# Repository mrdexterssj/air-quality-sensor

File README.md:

# Air quality sensor with OLED screen

A custom CO2 detector that displays the information on an OLED screen and has a LED Alarm. Made for Half Life W4! #YSWS

## Features 

* Uses the MQ-135 air quality sensor to detect the ppm os different nocive gases present in the air surrounding the device
* Has an 0.96 inches OLED screen to display the sensor's information and recommendations
* Has an alarm feature, where if the ppm exceed a certain threshold, an LED starts blinking and the screen shows a warning
* The alarm includes a buzzer that makes sounds at the same time the LED blinks (not added to the firmware yet)
* It also has a button the user can click to snooze the alarm for a minute. After that time passes, the sensor may trigger the alarm again if the ppm hadn't dropped below the predefined threshold
* It uses a XIAO-ESP32-C3 as the microcontroller

## Firmware

The firmware is a python script designed to run in MicroPython. It uses the standard libraries, together with an [external libaray](https://github.com/rubfi/MQ135) to get the readings from the MQ-135 module, and MicroPython's official [ssd1306](https://github.com/micropython/micropython-lib/blob/master/micropython/drivers/display/ssd1306/ssd1306.py) library. 

All the firmware can be found in `/firmware`.

The firmware was written in VSCode, using the `micropython-stubs` pip package, installed in a venv, with some special settings found in `/.vscode/settings.json`

## Production

Gerbers were generated using `Fabrication Toolkit`, a KiCad plugin that generates gerbers and drill files following JLCPCB guidelines and requirements.

They can be found inside `/co2-detector/production` as files, and compressed in `/gerbers.zip`.

## BOM Table

| **Item**                 | **Qty** | **Supplier**  | **Cost/item** | **Total Cost** | **link**                                                                                                                                            | **Note**                                                                    |
|--------------------------|---------|---------------|---------------|----------------|-----------------------------------------------------------------------------------------------------------------------------------------------------|-----------------------------------------------------------------------------|
| 0.96 OLED                | 1       | Temu          | $5.00         | $5.00          | https://www.temu.com/ec/2-piezas--de-pantalla-oled-de-0-96-pulgadas-12864-128x64--vcc-start-----pantalla-de--compatible-con--g-605685932739878.html |                                                                             |
| XIAO-ESP32-C3            | 1       | Seeed Studio  | $4.90         | $4.90          | https://www.seeedstudio.com/Seeed-XIAO-ESP32C3-p-5431.html                                                                                          |                                                                             |
| MQ-135                   | 1       | Novatronic EC | $4.50         | $4.50          | https://novatronicec.com/index.php/product/mq-135-sensor-calidad-de-aire/                                                                           | In person order, so no shipping                                             |
| PCB                      | 1       | Novatronic EC | $3.00         | $3.00          | https://novatronicec.com/index.php/product/fabricacion-de-circuitos-impresos-pcb/                                                                   | In person order, so no shipping                                             |
| Red LED                  | 1       | Local store   | $0.05         | $0.05          | N/A                                                                                                                                                 | I already have it                                                           |
| Small button             | 1       | Local store   | $0.05         | $0.05          | N/A                                                                                                                                                 | I already have it                                                           |
| Buzzer                   | 1       | Temu          | $2.46         | $2.46          | https://www.temu.com/ec/10-piezas---3v-5v-12v--magnetico--con--de-pitido-largo-y--12095-12-9-5mm-tmb12a03-tmb12a05-tmb12a12-g-605865197328055.html  | I may be able to buy this in person, but in case I can't I'm putting a link |
|                          |         |               |               |                |                                                                                                                                                     |                                                                             |
| Estimated total shipping | 1       |               |               | $8.73          |                                                                                                                                                     |                                                                             |

## Screenshots

_The PCB Layout_

_Front render_

_Back render_

_The schematic_

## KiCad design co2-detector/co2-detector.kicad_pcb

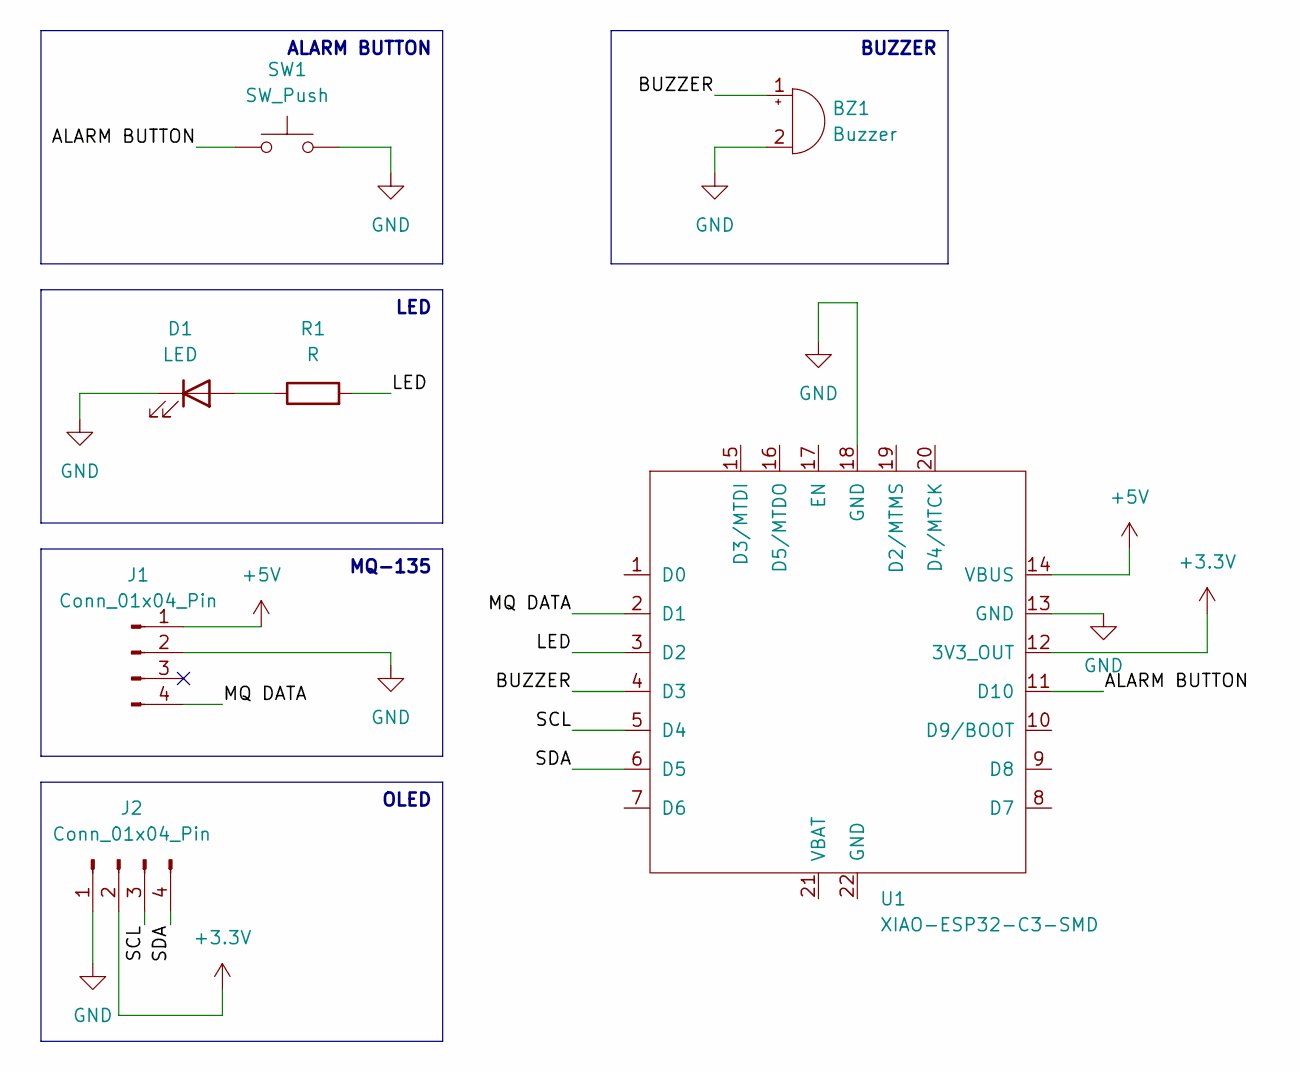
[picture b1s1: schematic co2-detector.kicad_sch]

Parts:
BZ1: Buzzer; Buzzer_12x9.5RM7.6
D1: LED; LED_D5.0mm
J1: Conn_01x04_Pin; PinHeader_1x04_P2.54mm_Vertical
J2: Conn_01x04_Pin; Display_128x64_096_I2C
R1: R; R_Axial_DIN0204_L3.6mm_D1.6mm_P7.62mm_Horizontal
SW1: SW_Push; SW_PUSH_6mm
U1: XIAO-ESP32-C3-SMD

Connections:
+3.3V: J2.2, U1.12 (3V3_OUT)
+5V: J1.1, U1.14 (VBUS)
/ALARM BUTTON: SW1.1, U1.11 (D10)
/BUZZER: BZ1.1 (+), U1.4 (D3)
/LED: R1.2, U1.3 (D2)
/MQ DATA: J1.4, U1.2 (D1)
/SCL: J2.3, U1.5 (D4)
/SDA: J2.4, U1.6 (D5)
GND: BZ1.2 (-), D1.1 (K), J1.2, J2.1, SW1.2, U1.13 (GND), U1.18 (GND)
unnamed: D1.2 (A), R1.1

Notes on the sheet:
BUZZER
MQ-135
OLED
ALARM BUTTON
LED

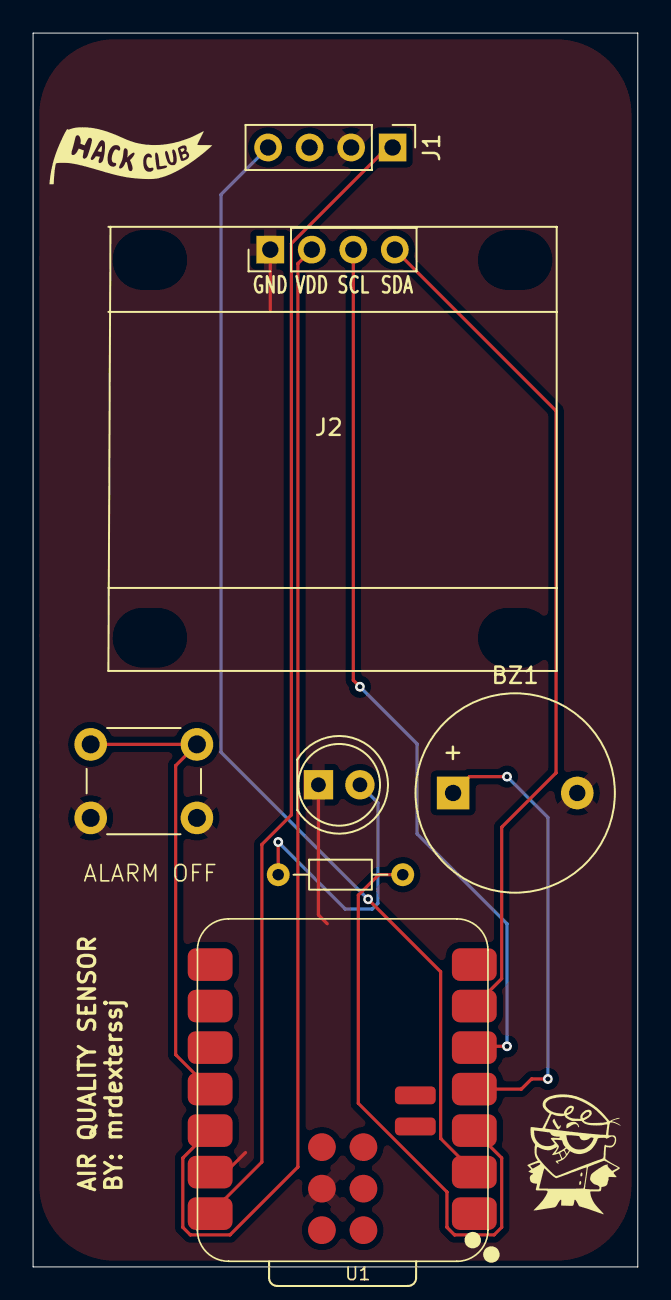
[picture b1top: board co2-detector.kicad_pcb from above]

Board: 2 copper layers, 37.0 x 75.5 mm, 7 parts (0 on the bottom side), 10 nets.
